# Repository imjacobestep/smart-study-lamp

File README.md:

This contains the main code for a smart study lamp prototype made as a project for GIX TECHIN 515 Hardware/Software Lab 2 in Spring 2022

# Variables:
These values are centralized in utilities.py: <br />
pin numbers <br />
color values <br />
crop dimensions (box above finger, for text extraction) <br />
target brightness <br />
finger jitter correction tolerance <br />
word distance-from-finger margin <br />

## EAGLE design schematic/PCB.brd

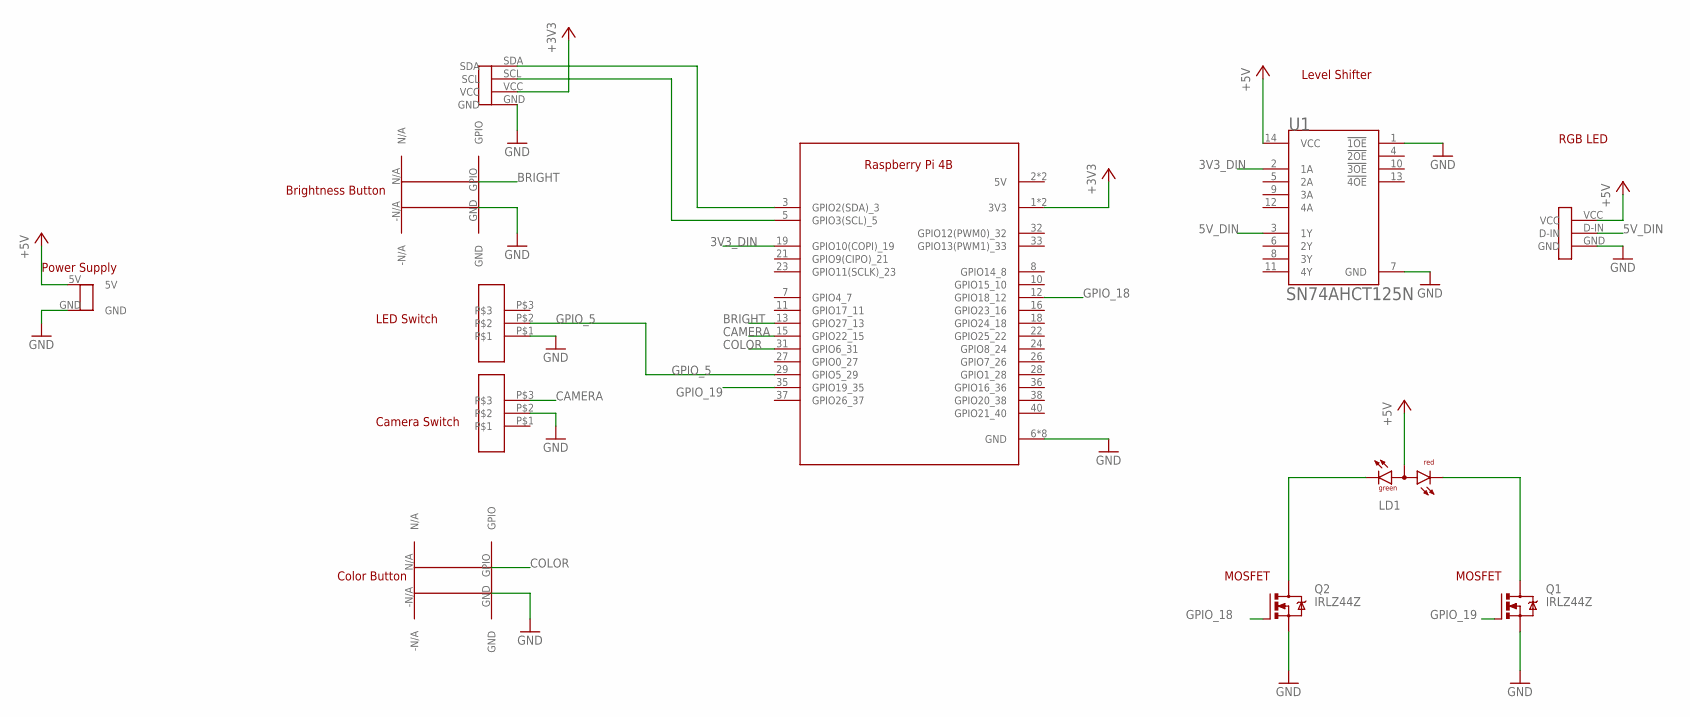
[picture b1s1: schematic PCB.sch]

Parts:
LD1: DUOLED-RG-A; DUOLED-A-5MM
Q1, Q2: IRLZ44Z; TO220BH
U1: TEXAS_INSTRUMENTS_SN74AHCT125NTEXAS_INSTRUMENTS_S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; TEXAS_INSTRUMENTS_SN74AHCT125N_0
U$1: RASPBERRY_PI_4; RASPI_4B
U$2, U$3: G13-SW
U$4: LIGHTSENSOR-PO; LIGHTSENSOR-IO
U$5: LED-STRIP-PO
U$6, U$7: G13-BUTTON
U$8: G13-BATTERY

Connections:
3V3_DIN: U1.2 (1A), U$1.19 (GPIO10(COPI)_19)
5V_DIN: U1.3 (1Y), U$5.D-IN
+3V3: U$1.1 (3V3), U$1.17 (3V3), U$4.VCC
+5V: LD1.A, U1.14 (VCC), U$5.VCC, U$8.5V
BRIGHT: U$1.13 (GPIO27_13), U$6.GPIO
CAMERA: U$1.15 (GPIO22_15), U$3.P$3
COLOR: U$1.31 (GPIO6_31), U$7.GPIO
GND: Q1.S, Q2.S, U1.1 (!1OE!), U1.7 (GND), U$1.6 (GND), U$1.9 (GND), U$1.14 (GND), U$1.20 (GND), U$1.25 (GND), U$1.30 (GND), U$1.34 (GND), U$1.39 (GND), U$2.P$1, U$3.P$2, U$4.GND, U$5.GND, U$6.GND, U$7.GND, U$8.GND
GPIO_5: U$1.29 (GPIO5_29), U$2.P$2
GPIO_18: Q2.G, U$1.12 (GPIO18_12)
GPIO_19: Q1.G, U$1.35 (GPIO19_35)
unnamed: U$1.3 (GPIO2(SDA)_3), U$4.SDA
unnamed: U$1.5 (GPIO3(SCL)_5), U$4.SCL
unnamed: LD1.CR, Q1.D
unnamed: LD1.CX (CG), Q2.D

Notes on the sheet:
Brightness Button
Color Button
Level Shifter
Power Supply
MOSFET
RGB LED
LED Switch
Camera Switch

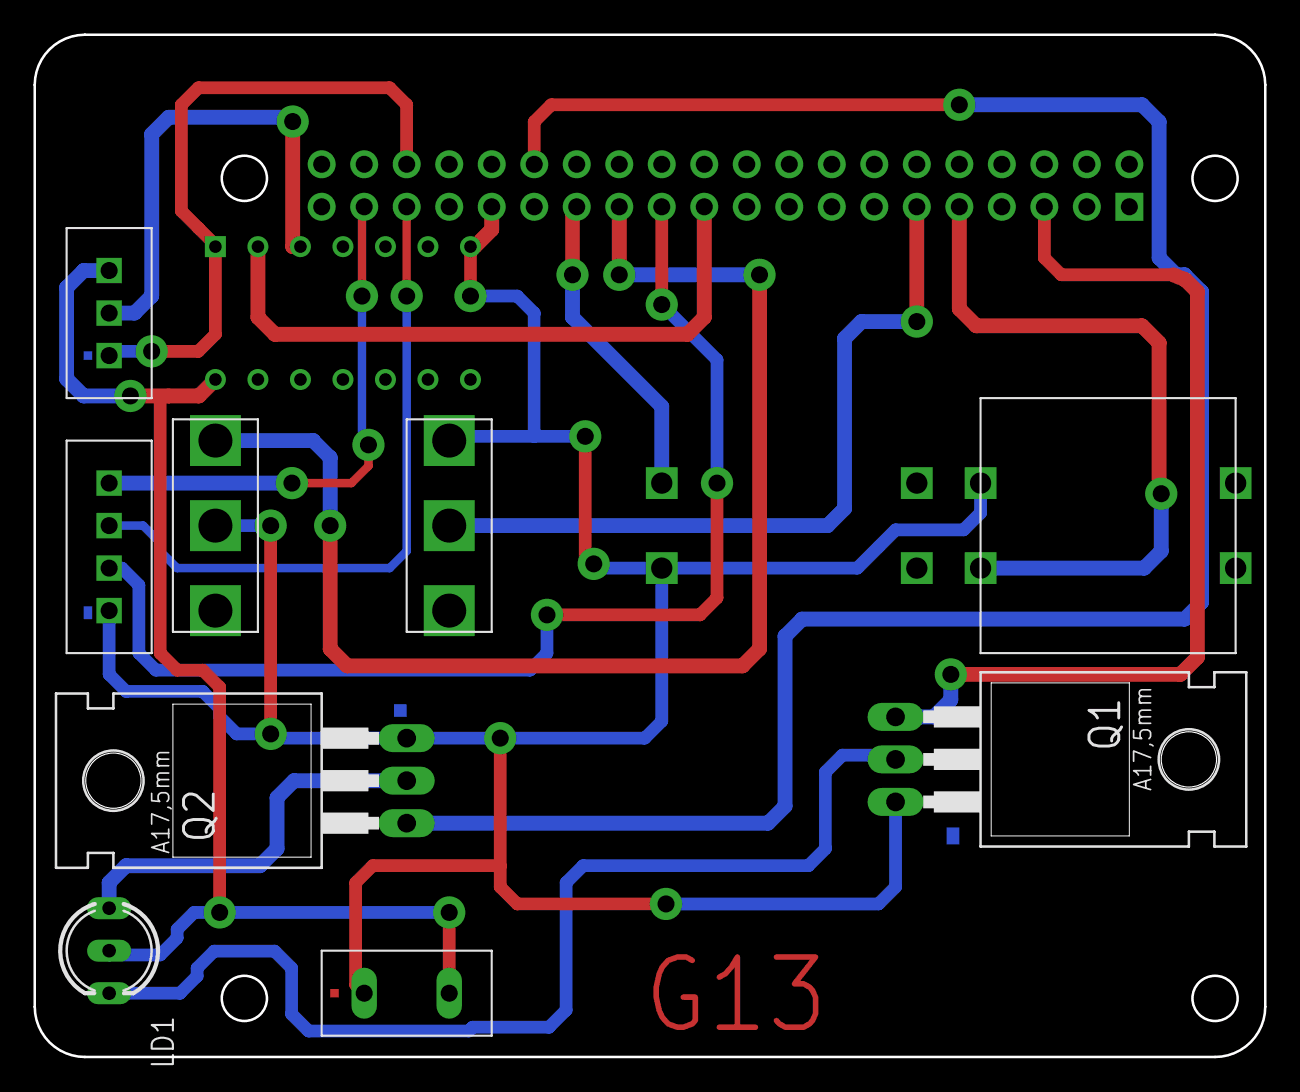
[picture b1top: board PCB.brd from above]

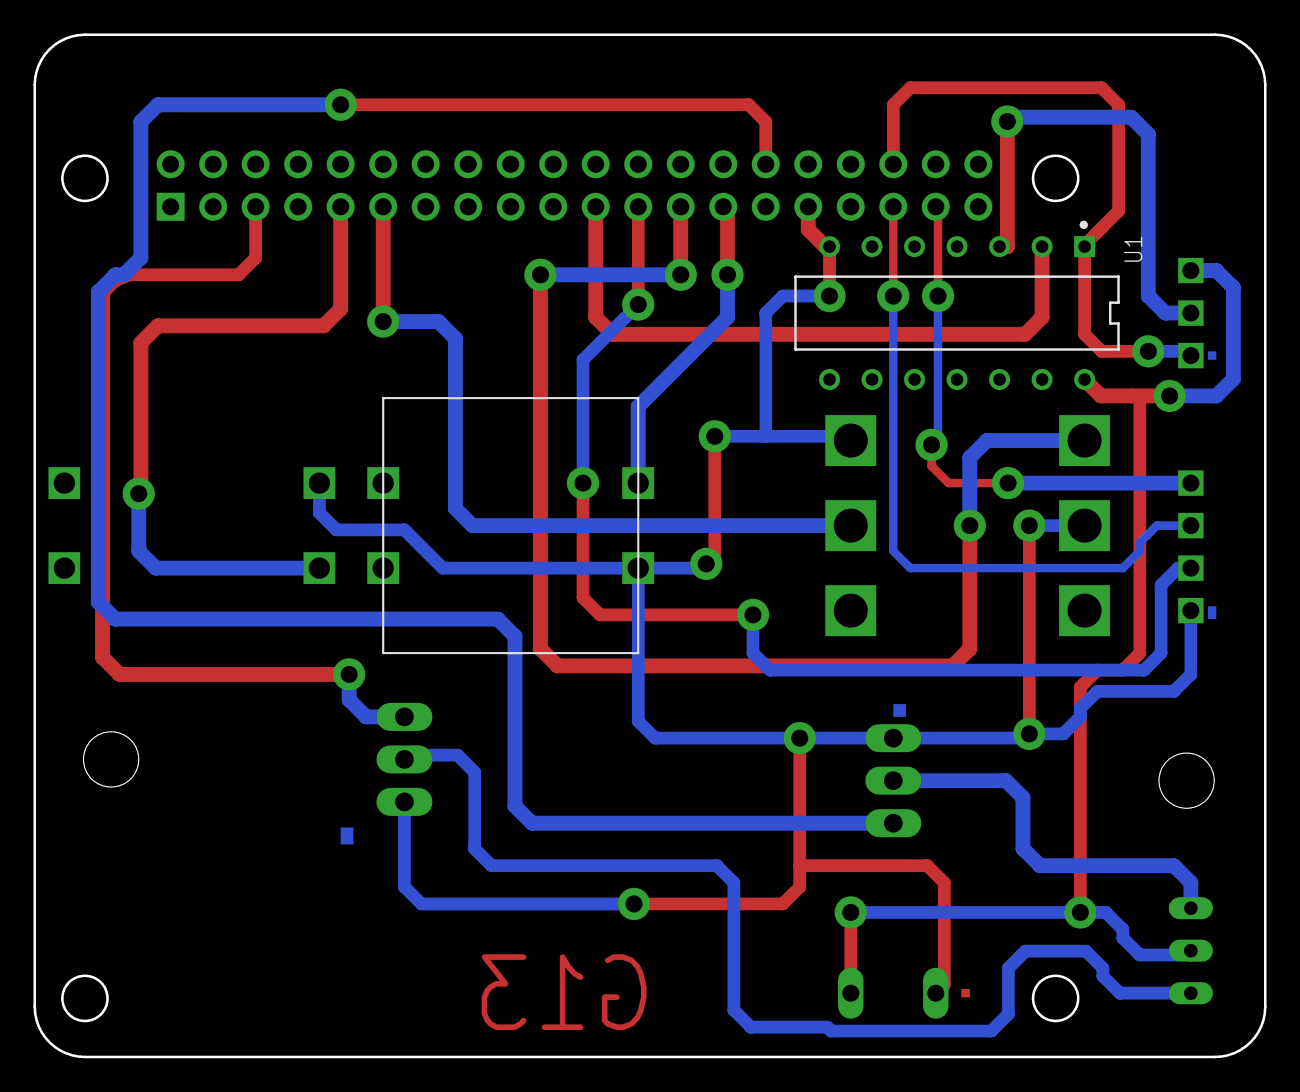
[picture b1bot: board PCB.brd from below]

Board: 2 copper layers, 73.5 x 61.1 mm, 12 parts (2 on the bottom side), 15 nets.

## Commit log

2022-04-11 Added initial info to readme
2022-04-12 Created using Colaboratory
2022-04-12 Added some potential python library links
2022-04-12 Added dictionary library for definitions
2022-04-12 Added blank test code files and a few test images to run through skew and ocr code
2022-04-15 Added a bunch of things!
    I added test code files for each function and a main file with all of them centralized. So far, everything works in theory, but OCR (text-detection) output is not useful
2022-04-15 OCR adjustments
    I tweaked some of the OCR test code, it got a little better output from closer crops of test images
2022-04-17 I added the tweaked cropping file and the related changes to the OCR test
2022-04-17 changed skew correction
2022-04-17 Added camera button code into lamp.py
2022-04-17 Tested OCR with more images, added initial page detection file
2022-04-22 Added gesture tracking
    I got the gesture tracking test code working. A swipe gesture will trigger a "page turn" and a point (after lingering for a few seconds) will trigger the word lookup feature for the word the fingerti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
2022-04-29 Worked on consolidating code. Camera service is mostly done, initial multithreading
2022-04-29 Organized, consolidated code and files
    I organized test images and code files into folders. I also worked more on the consolidated code to bring it over to the Pi
2022-04-29 Forgot to hit save on one file before las push
2022-05-04 Added pin number table image
2022-05-06 New Pin numbers file
    Swapped the pin number image with an editable text file, now with updates values
2022-05-06 Edited the code to fit new process, added utility test code
2022-05-06 edited test file
2022-05-06 Updated all pin references to point back to pin table
2022-05-06 added camera test with live view
2022-05-06 some minor bug fixes, modified light service
2022-05-06 added auto color/brightness test
2022-05-06 fixed main test
2022-05-07 finger coords print error fixed
2022-05-07 fixed string formatting
2022-05-07 string formatting
2022-05-07 imports
2022-05-07 changed null returns
2022-05-07 created colors table
2022-05-08 Create setup
2022-05-08 tweaked code, added shell script that will (hopefully) automate library installs
2022-05-09 Changed pi username after new reset
2022-05-09 reorganized older test files, updated script
2022-05-09 camera switch bugfix
2022-05-09 camera change bugfix
2022-05-09 more testing
2022-05-09 updated packages script, bugfixes
2022-05-09 test
2022-05-09 fixed cropping (hopefully)
2022-05-09 more tests
2022-05-09 prep for m2 demo
2022-05-09 re-wrote ocr test to work on pi, hopefully to diagnose issues in m2
2022-05-10 added new ocr test using picamera
2022-05-13 rewrote test to show cropped area on preview
2022-05-13 added 3rd camera test method using still images
2022-05-16 got word finding working in test code, added into main code for testing
2022-05-17 updated ip address
2022-05-18 slight adjustment for word recognition crop
2022-05-19 updated pins
2022-05-20 finished new LED integration, streamlined everything else
2022-05-20 fixed color_update error
2022-05-20 fixed env test error
2022-05-20 fixed camera test issue
2022-05-23 added new LED changes to reduce flicker into main code
2022-05-24 Added sql queries and azure database info
2022-05-24 added methods to send data to database, included in main test
2022-05-26 added code to correct rgb color change over 255
2022-05-26 Added git commands and cheat sheet
2022-05-27 added print statements to camera toggle
2022-05-28 pin numbers update
2022-05-29 testing main loop fixes
2022-05-29 added print statements to main loop for clarity
2022-05-30 added test code for potential firestore database instead of sql
2022-05-30 Sumayyah: Checked that leds work (firebase disabled)
2022-05-30 added working db_test.py file
2022-06-01 added commands to send word and lux values
2022-06-01 added camera running print statements
2022-06-02 Fixed rgb LED issues when word selected
2022-06-04 adjusted timing of lux update
2022-06-05 modify led manual mode
2022-06-05 slowed voice down
2022-06-06 updated token
2022-06-06 added definition and word use to database
2022-06-06 added string formatting
2022-08-07 updated readme, removed server info
2022-08-07 Deleted firebase config file
